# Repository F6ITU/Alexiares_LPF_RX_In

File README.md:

# Alexiares_LPF_RX_In

THIS PROJECT IS DEPRECATED. DO NOT USE IT WITH ANGELIA/ALEX ARCHITECTURE
(could be used as a simple lpf with notch for any other short waves sdr project

Alex RX 7th order lpf with 88-108 rejection notch

This repository contains the High Pass Filter project of the OpenHPSDR Alexiares frontend

Originaly, this filter is located on the RX, HPF board of Alexiares. 
As the size of this hpf board is limited, it has been decided to 
put this lpf and the TX/RX relay (RXpath and Pure Signal path) on a 
specific board.

The filter is a 7th order lpf with 2 notch rejection frequecies 
centered on the FM broadcast band (88 and 108 MHz). Thus, very strong
FM radio station will not be received in the 4th Nyquist zone of 
the SDR.

A "watertight" rf shielding could be placed around the board or around 
the filter itself. 

The file lpf input.PNG gives a simulation of this filter

Part of this work is protected by the TAPR Open Hardware Licence https://www.tapr.org/ohl.html

Original work by Graham Haddock, KE9H and Phil Harman, VK6APH.

Board's dimensions are undersized to fit the 10x10cm 
size of all board of the Hermes project under Kicad: 

AlexI2C

Alexandrie

Alexiares_Coax_Out 

Alexiares_HPF 

Alexiares_LPF

Mentor

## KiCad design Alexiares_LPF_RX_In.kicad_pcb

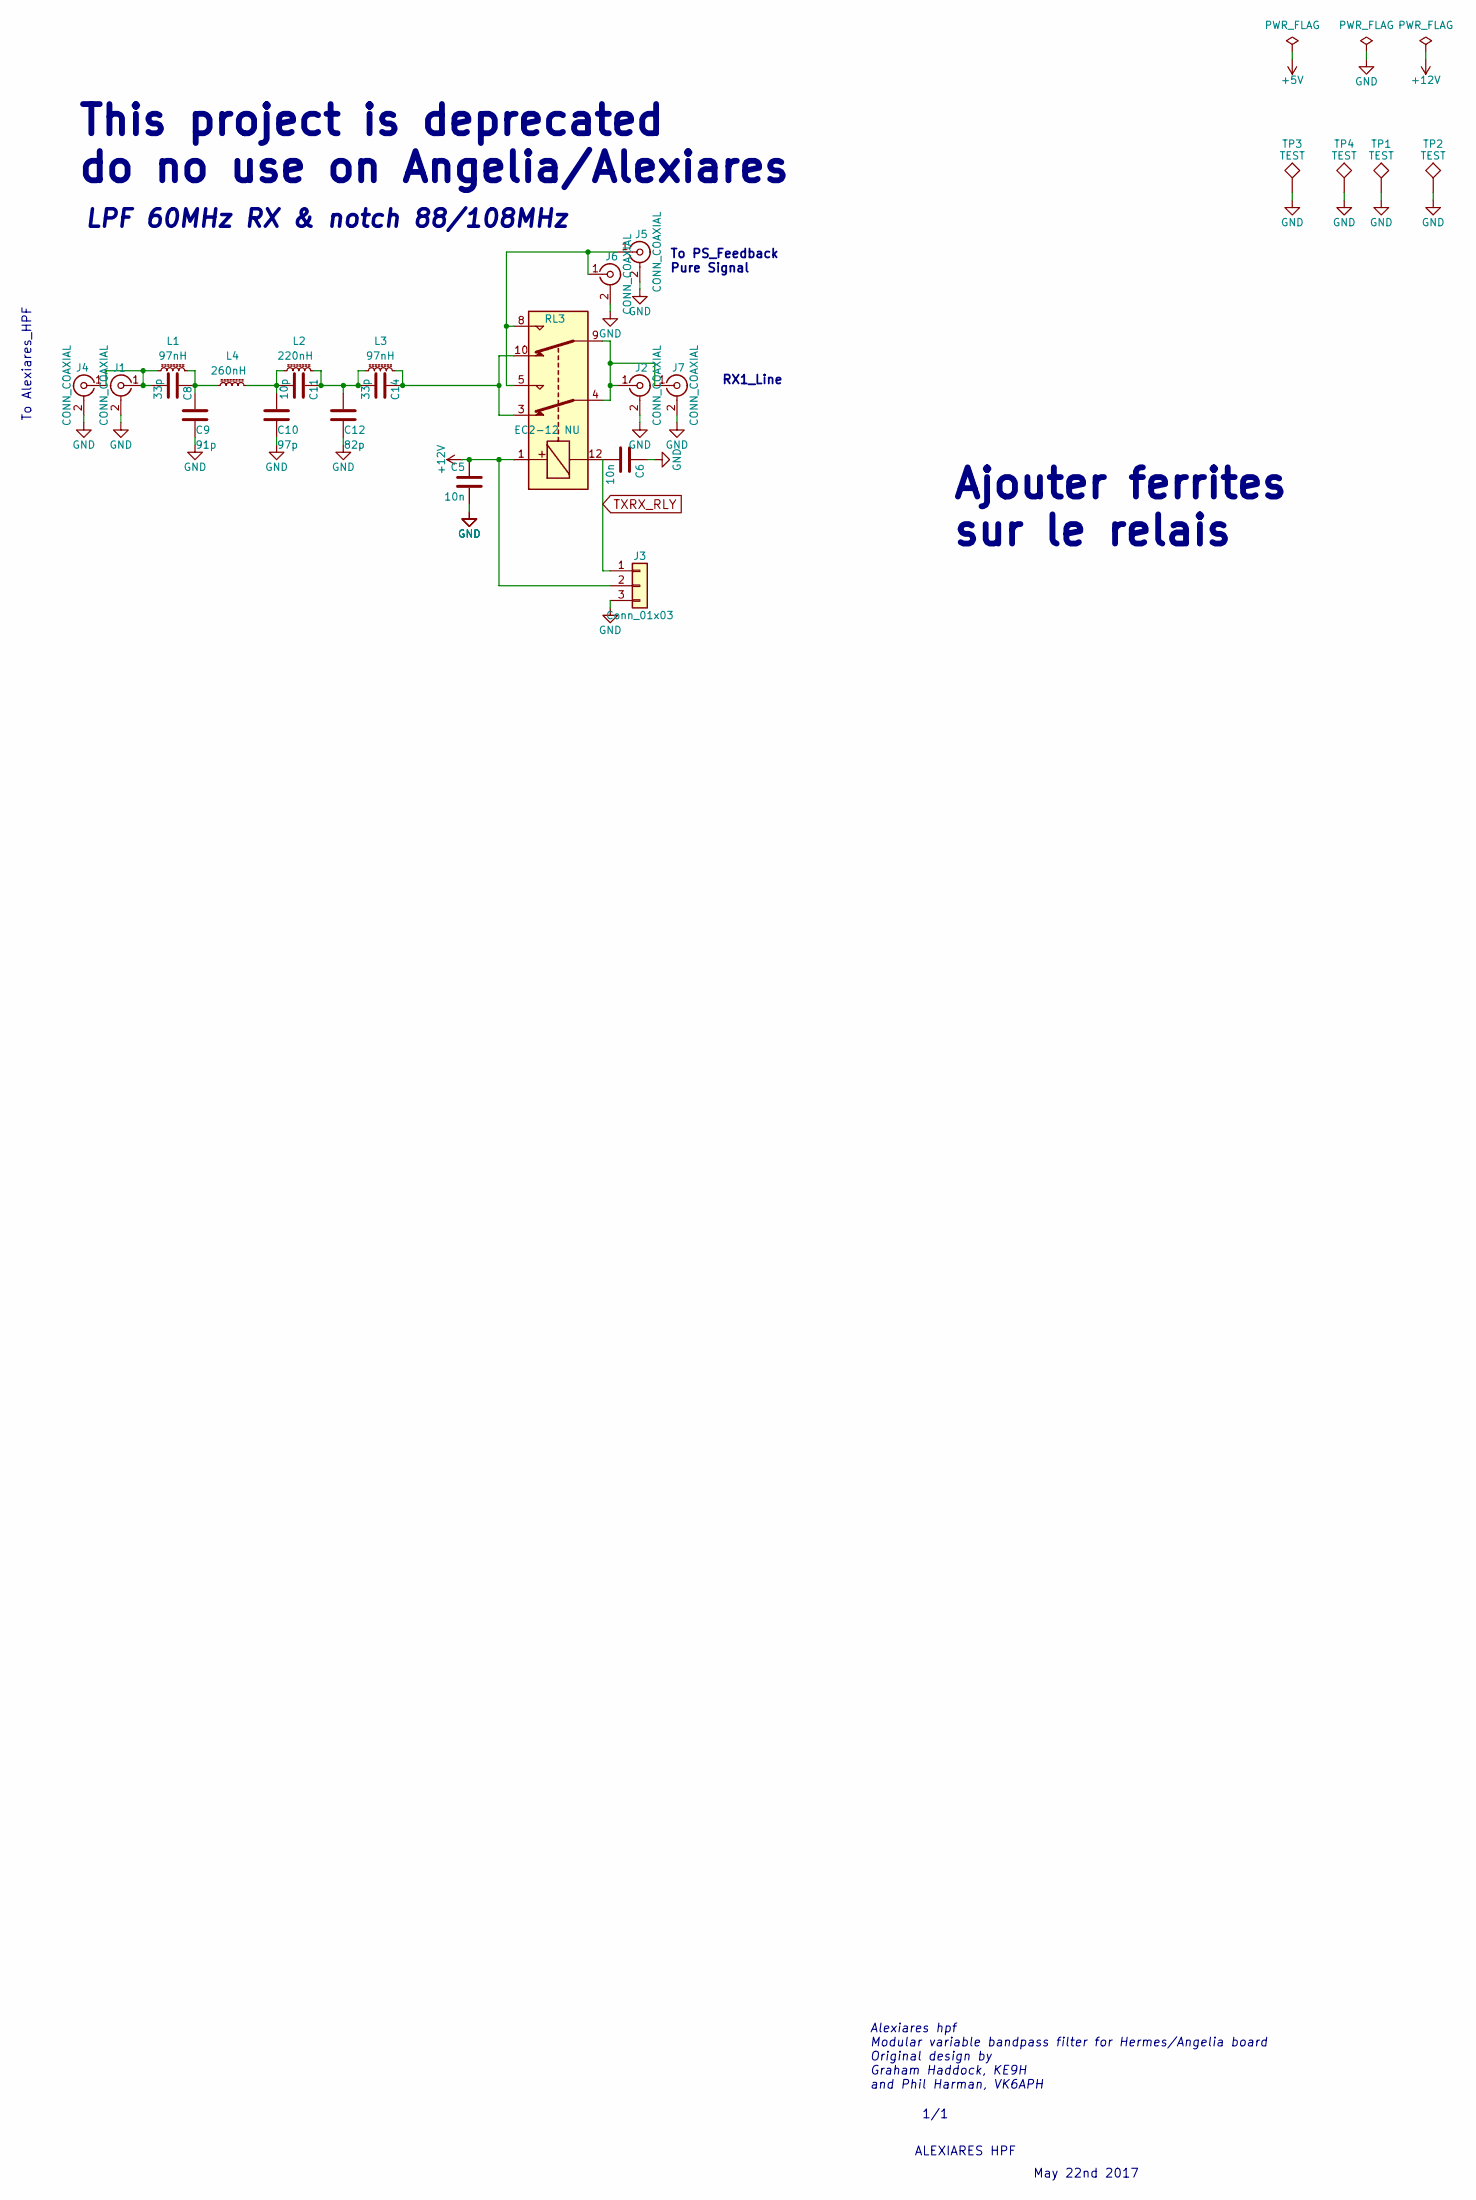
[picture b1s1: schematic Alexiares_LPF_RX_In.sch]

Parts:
C5, C6: 10n; C_0805_HandSoldering
C8, C14: 33p; ATC_500_HandSoldering
C9: 91p; ATC_500_HandSoldering
C10: 97p; ATC_500_HandSoldering
C11: 10p; ATC_500_HandSoldering
C12: 82p; ATC_500_HandSoldering
J1, J2, J5: CONN_COAXIAL; SMA_THT_Jack_Straight
J3: Conn_01x03; kk100_22-23-2031
J4, J6, J7: CONN_COAXIAL; SMA_EDGE_NRW
L1, L3: 97nH; T50_V_THT
L2: 220nH; T50_V_THT
L4: 260nH; T50_V_THT
RL3: EC2-12 NU; Relay_DPDT_NEC_EC2
TP1, TP2, TP3, TP4: TEST; MountingHole_3.5mm_Pad

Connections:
+12V: C5.1, J3.2, RL3.1
GND: C5.2, C6.1, C9.2, C10.2, C12.2, J1.2 (Ext), J2.2 (Ext), J3.3, J4.2 (Ext), J5.2 (Ext), J6.2 (Ext), J7.2 (Ext), TP1.1, TP2.1, TP3.1, TP4.1
unnamed: C8.1, C9.1, L1.2, L4.1
unnamed: C8.2, J1.1 (In), J4.1 (In), L1.1
unnamed: C10.1, C11.2, L2.1, L4.2
unnamed: C11.1, C12.1, C14.2, L2.2, L3.1
unnamed: C14.1, L3.2, RL3.3, RL3.10
unnamed: J2.1 (In), J7.1 (In), RL3.4, RL3.9
unnamed: J5.1 (In), J6.1 (In), RL3.5, RL3.8
TXRX_RLY: C6.2, J3.1, RL3.12

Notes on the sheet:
Alexiares hpf Modular variable bandpass filter for Hermes/Angelia board Original design by Graham Haddock, KE9H and Phil Harman, VK6APH
1/1
ALEXIARES HPF
May 22nd 2017
RX1_Line
This project is deprecated do no use on Angelia/Alexiares
To PS_Feedback Pure Signal
LPF 60MHz RX & notch 88/108MHz
To Alexiares_HPF
Ajouter ferrites sur le relais

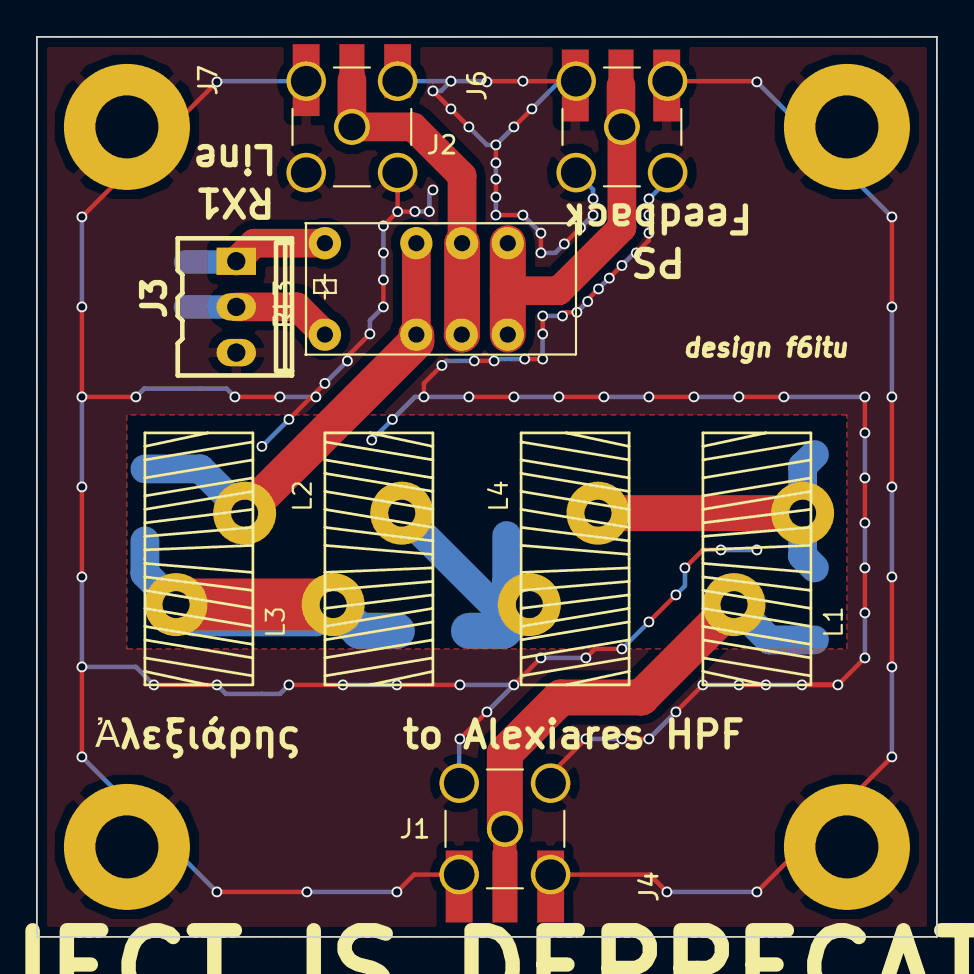
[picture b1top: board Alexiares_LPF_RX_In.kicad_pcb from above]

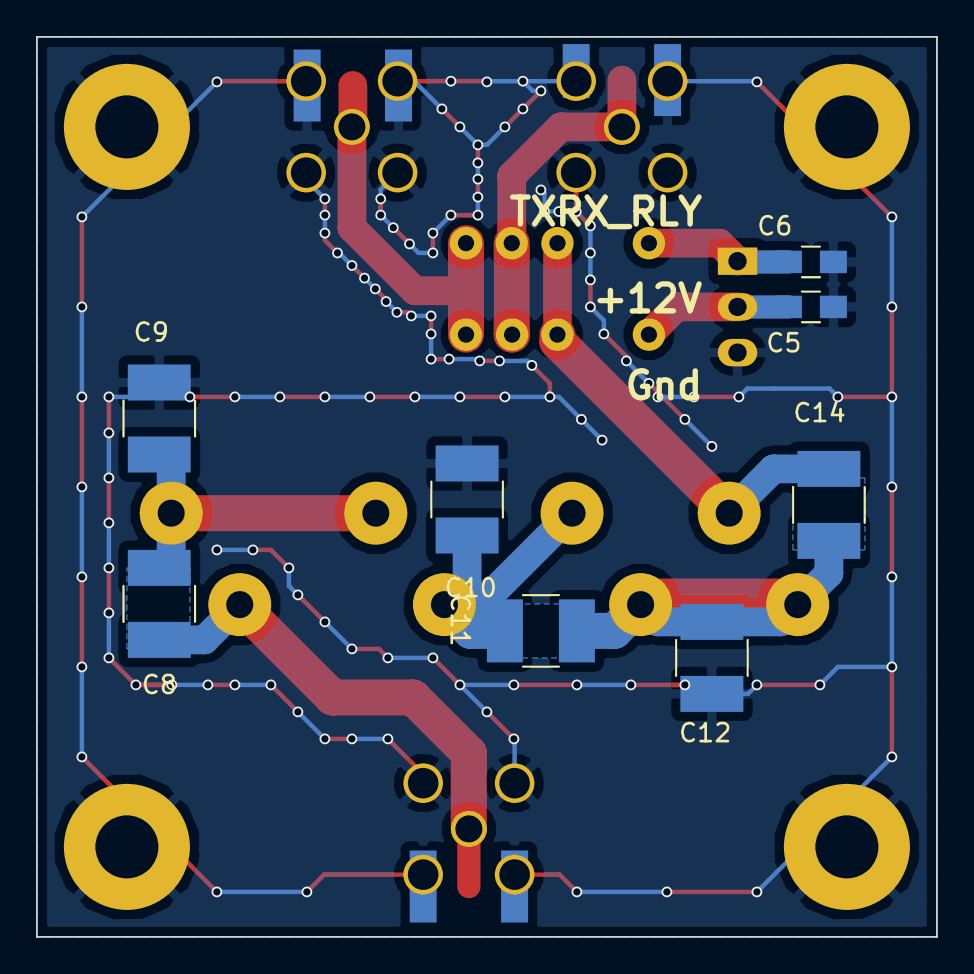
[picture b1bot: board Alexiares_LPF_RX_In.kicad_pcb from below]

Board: 2 copper layers, 50.0 x 50.0 mm, 24 parts (8 on the bottom side), 10 nets.

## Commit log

2017-11-10 First commit and RTM
2017-11-14 Caps changed for ATC footprint
2017-11-27 some via added
2017-12-31 DEPRECATED PROJECT, DO NOT USE WITH ALEX
